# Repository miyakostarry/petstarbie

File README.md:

CATBIE (STARBIE)

A small digital pet that lives inside a cat-shaped case. It shows a pet on a screen and reacts when you move it, press it's buttons or touch it.

How it works╰(*°▽°*)╯

> An ESP32 board is the brain, It runs the pet program.
> A screen shows the pet.
> A gyro sensor feels when you tilt or shake the cat.
> Two buttons and a touch pad let you interact with it.
> A temperature sensor lets the pet react to the room.
> A rechargeable battery powers it. A charger module charges it over USB, and a power switch turns it on and off.

All the parts plug into sockets on a cat-shaped PCB (designed in KiCad). The board sits inside a 3D-printed cat shell.

 Parts  (≧∀≦)ゞ

- ESP32 DevKit V1 (30-pin)
- 1.8" ST7735 SPI TFT display
- MPU6050 (GY-521) gyro
- DHT11 module
- 2 tactile push buttons
- 2 resistors, 100 kΩ
- JST-PH battery connector
- 3.7 V LiPo battery
- TP4056 charger module
- MT3608 boost converter

## Bill of Materials (BOM) (｡•̀ᴗ-)✧

Here's the list of components used for CATBIE, along with their estimated prices and suppliers. Prices may vary depending on availability and shipping.

| Component                                    |   Quantity | Supplier     | Cost per Item (USD) | Total Cost (USD) | Link                                                                                               |
| -------------------------------------------- | ---------: | ------------ | ------------------: | ---------------: | -------------------------------------------------------------------------------------------------- |
| ESP32 DevKit V1 (30-pin)                     |          1 | Amazon India |               $5.60 |            $5.60 | [View product](https://www.amazon.in/SP-ELECTRON-ESP32-Development-ESP32-WROOM-32/dp/B0HD7QC26L/)  |
| MPU6050 (GY-521)                             |          1 | Amazon India |               $3.40 |            $3.40 | [View product](https://www.amazon.in/dp/B07H3XH1TB)                                                |
| 1.8" ST7735 SPI TFT Display                  |          1 | Robu.in      |               $3.50 |            $3.50 | [View product](https://robu.in/product/1-8-inch-spi-128160-tft-lcd-display-module-pcb-arduino/)    |
| DHT11 Temperature and Humidity Sensor Module |          1 | Robu.in      |               $0.56 |            $0.56 | [View product](https://robu.in/product/dht11-digital-relative-humidity-temperature-sensor-module/) |
| Tactile Push Button                          |          1 | Robu.in      |               $0.25 |            $0.25 | [View product](https://robu.in/product/6x6x5-tactile-push-button-switch/)                          |
| 100 kΩ Resistor                              |          2 | Robu.in      |               $0.20 |            $0.40 | [View product](https://robu.in/product/100k-ohm-0-5w-metal-film-resistor-pack-of-50/)              |
| 3.7 V, 500 mAh LiPo Battery with JST-PH      |          1 | Amazon India |   $3.00 (estimated) |            $3.00 | [Search products](https://www.amazon.in/s?k=3.7V+500mAh+lipo+battery+JST+PH)                       |
| TP4056 USB-C Charger Module with Protection  |          1 | Amazon India |               $1.00 |            $1.00 | [View product](https://www.amazon.in/UNIVERSAL-HUB-TP4056-Overcharge-Protection/dp/B0FVLYQBKC/)    |
| MT3608 Boost Converter                       |          1 | Amazon India |               $1.40 |            $1.40 | [View product](https://www.amazon.in/Hexonix-Voltage-Booster-Adjustable-Converter/dp/B0HDP881HN/)  |
| Custom PCB                                   |          1 | JLCPCB       |   $5.20 (estimated) |            $5.20 | [JLCPCB](https://jlcpcb.com/)                                                                      |
| Estimated Shipping                           | 1 shipment | JLCPCB       |                   — |            $9.83 | —                                                                                                  |

### Estimated Project Cost

| Category              | Estimated Cost (USD) |
| --------------------- | -------------------: |
| Electronic components |               $19.11 |
| Custom PCB            |                $5.20 |
| Estimated shipping    |                $9.83 |
| **Estimated Total**   |           **$34.14** |

> **Note:** These are estimated prices, not a confirmed final bill. Shipping, taxes, customs charges, and component prices may change. The battery price is approximate because different sellers offer different options.

AI help is taken to understand how connections and components work and also help taken from people in how to use kiCAD and one of my friend helped me picking up the components to use so yeah he helped alot 
another thing i want to add that my friend created the structure shell for my catbie/neckobie in blender but i'm having trouble opening the fbx file in blender so i couldn't post the image of it

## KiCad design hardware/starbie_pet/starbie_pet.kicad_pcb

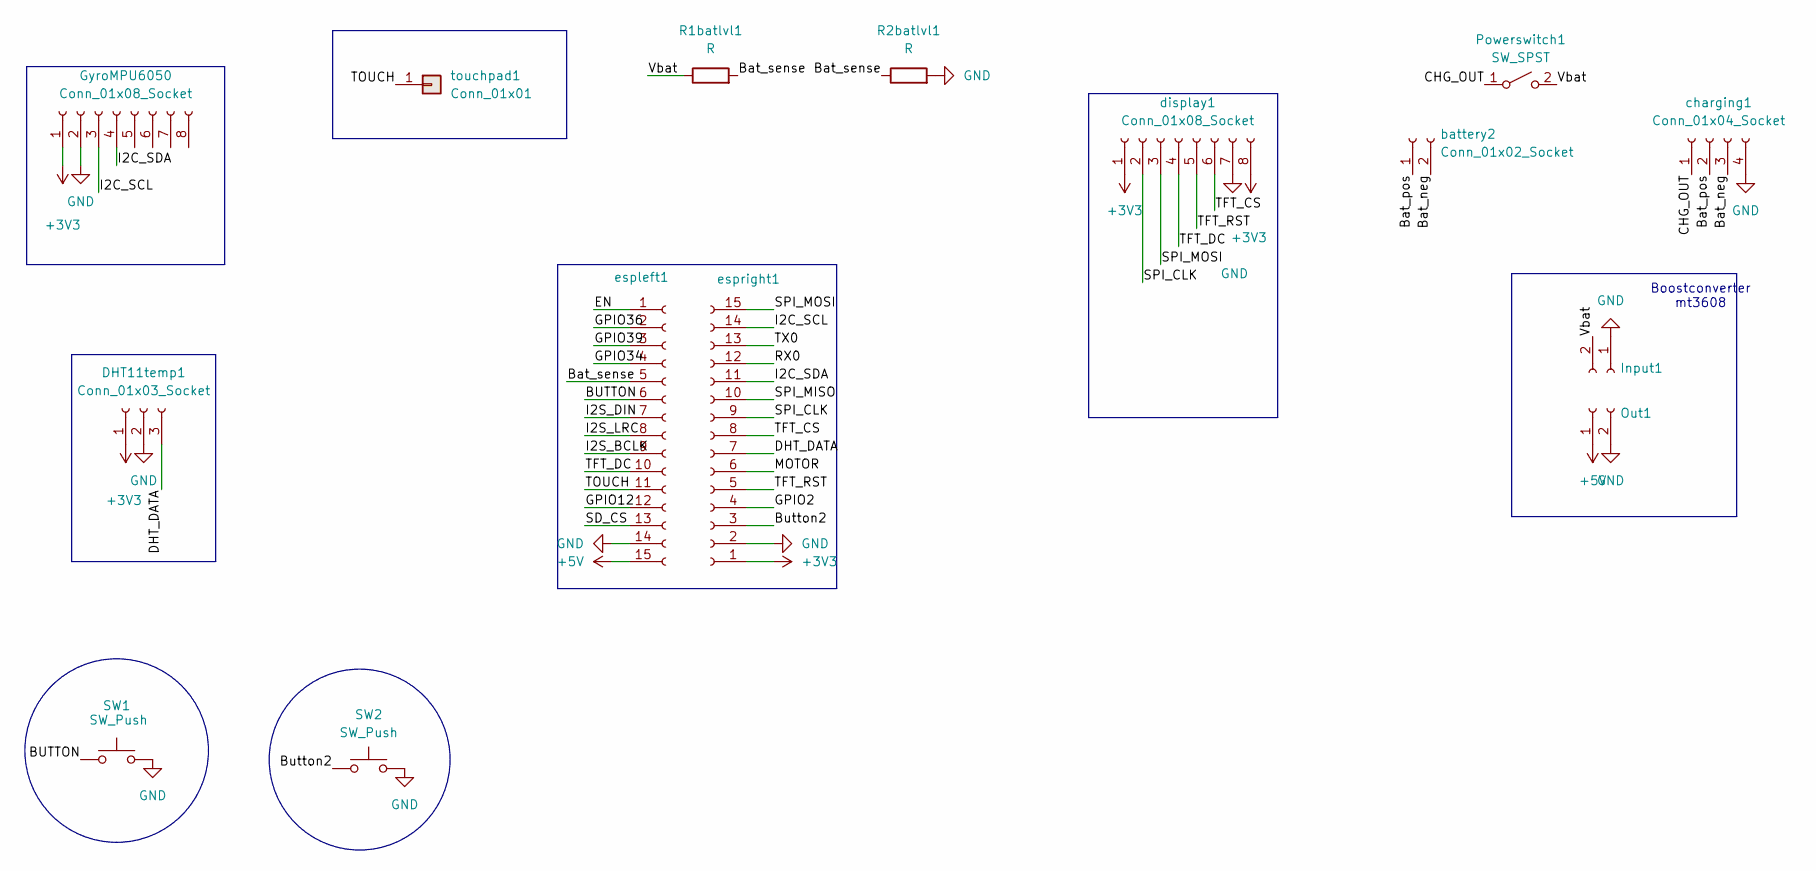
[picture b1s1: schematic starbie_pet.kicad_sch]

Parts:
DHT11temp1: Conn_01x03_Socket; PinSocket_1x03_P2.54mm_Vertical
GyroMPU6050: Conn_01x08_Socket; PinSocket_1x08_P2.54mm_Vertical
Input1: Conn_01x02_Socket; PinHeader_1x02_P2.54mm_Vertical
Out1: Conn_01x02_Socket; PinHeader_1x02_P2.54mm_Vertical
Powerswitch1: SW_SPST; FanPinHeader_1x03_P2.54mm_Vertical
R1batlvl1, R2batlvl1: R; R_Axial_DIN0207_L6.3mm_D2.5mm_P2.54mm_Vertical
SW1, SW2: SW_Push; SW_PUSH_6mm
battery2: Conn_01x02_Socket; JST_PH_B2B-PH-K_1x02_P2.00mm_Vertical
charging1: Conn_01x04_Socket; FanPinHeader_1x04_P2.54mm_Vertical
display1: Conn_01x08_Socket; PinSocket_1x08_P2.54mm_Vertical
espleft1: Conn_01x15_Socket; PinSocket_1x15_P2.54mm_Vertical
espright1: Conn_01x15_Socket; PinSocket_1x15_P2.54mm_Vertical
touchpad1: Conn_01x01; TestPoint_Pad_D4.0mm

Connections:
+3V3: DHT11temp1.1, GyroMPU6050.1, display1.1, display1.8, espright1.1
+5V: Out1.1, espleft1.15
/BUTTON: SW1.1, espleft1.6
/Bat_neg: battery2.2, charging1.3
/Bat_pos: battery2.1, charging1.2
/Bat_sense: R1batlvl1.2, R2batlvl1.1, espleft1.5
/Button2: SW2.1, espright1.3
/CHG_OUT: Powerswitch1.1 (A), charging1.1
/DHT_DATA: DHT11temp1.3, espright1.7
/EN: espleft1.1
/GPIO2: espright1.4
/GPIO12: espleft1.12
/GPIO34: espleft1.4
/GPIO36: espleft1.2
/GPIO39: espleft1.3
/I2C_SCL: GyroMPU6050.3, espright1.14
/I2C_SDA: GyroMPU6050.4, espright1.11
/I2S_BCLK: espleft1.9
/I2S_DIN: espleft1.7
/I2S_LRC: espleft1.8
/MOTOR: espright1.6
/RX0: espright1.12
/SD_CS: espleft1.13
/SPI_CLK: display1.2, espright1.9
/SPI_MISO: espright1.10
/SPI_MOSI: display1.3, espright1.15
/TFT_CS: display1.6, espright1.8
/TFT_DC: display1.4, espleft1.10
/TFT_RST: display1.5, espright1.5
/TOUCH: espleft1.11, touchpad1.1 (Pin_1_1)
/TX0: espright1.13
/Vbat: Input1.2, Powerswitch1.2 (B), R1batlvl1.1
GND: DHT11temp1.2, GyroMPU6050.2, Input1.1, Out1.2, R2batlvl1.2, SW1.2, SW2.2, charging1.4, display1.7, espleft1.14, espright1.2

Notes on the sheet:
Boostconverter mt3608

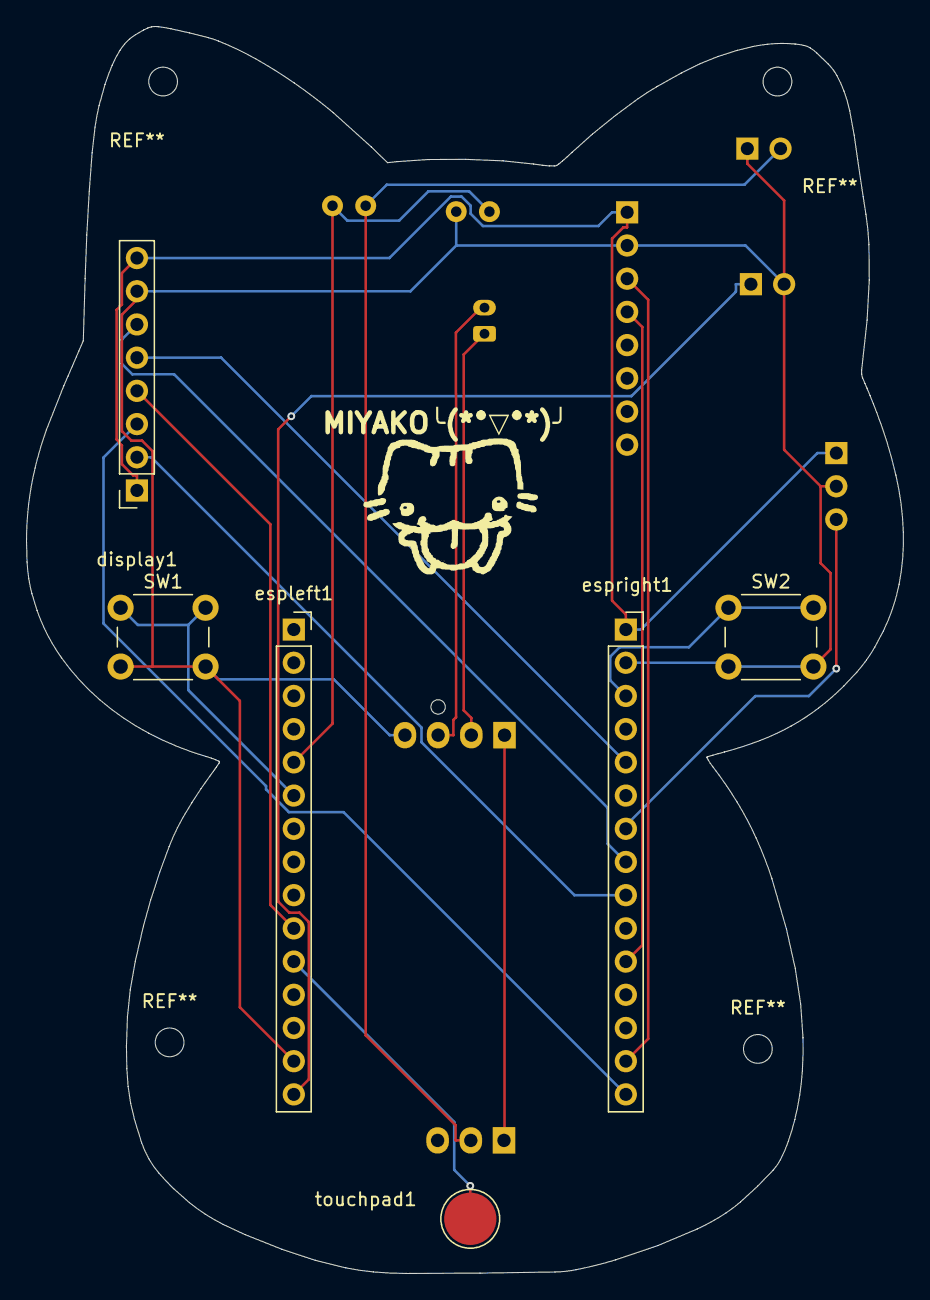
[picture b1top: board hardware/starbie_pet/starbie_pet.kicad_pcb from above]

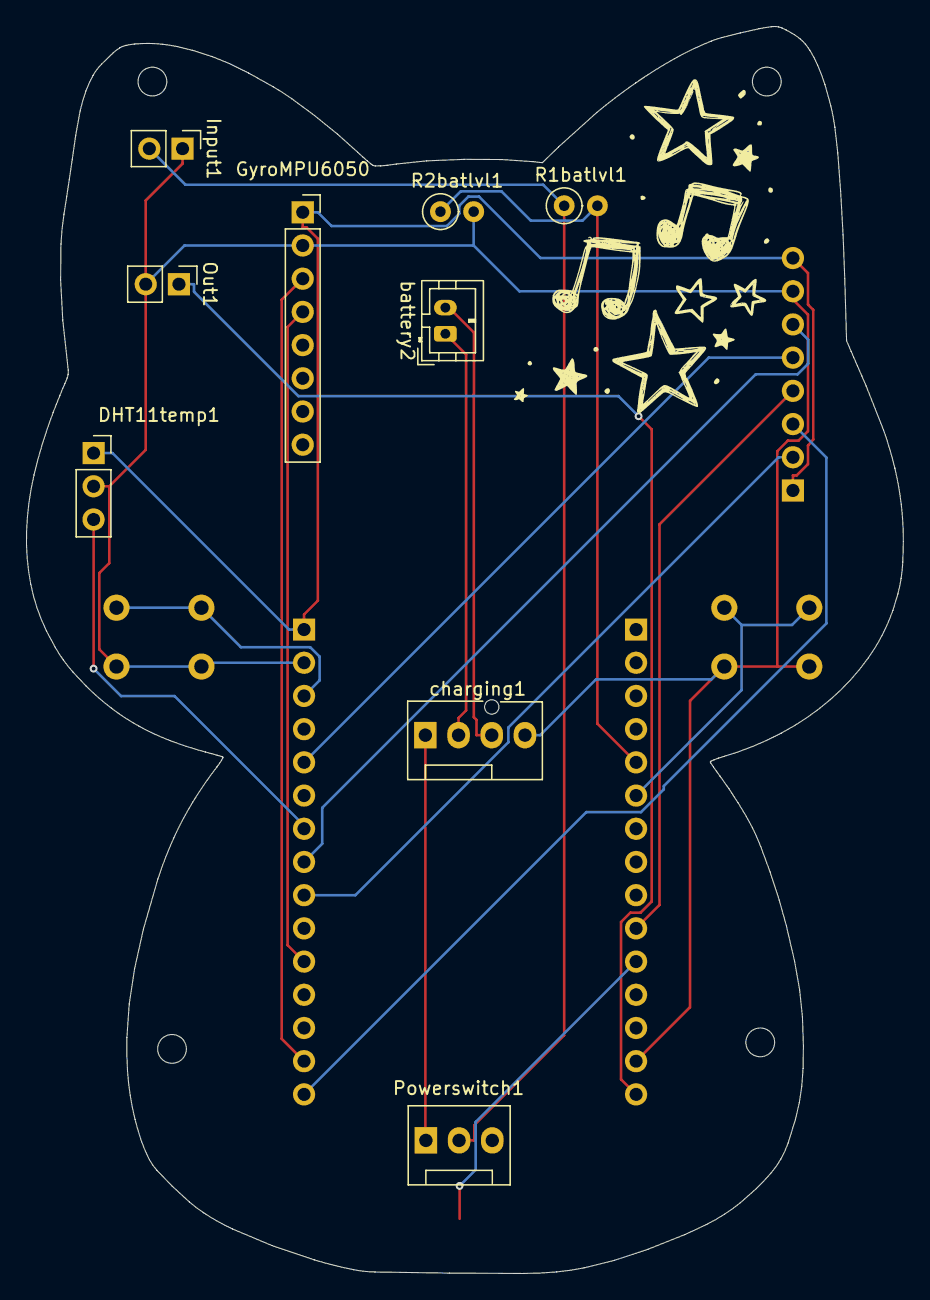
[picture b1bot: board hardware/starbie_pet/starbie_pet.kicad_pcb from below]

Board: 2 copper layers, 67.1 x 95.4 mm, 15 parts (9 on the bottom side), 19 nets.

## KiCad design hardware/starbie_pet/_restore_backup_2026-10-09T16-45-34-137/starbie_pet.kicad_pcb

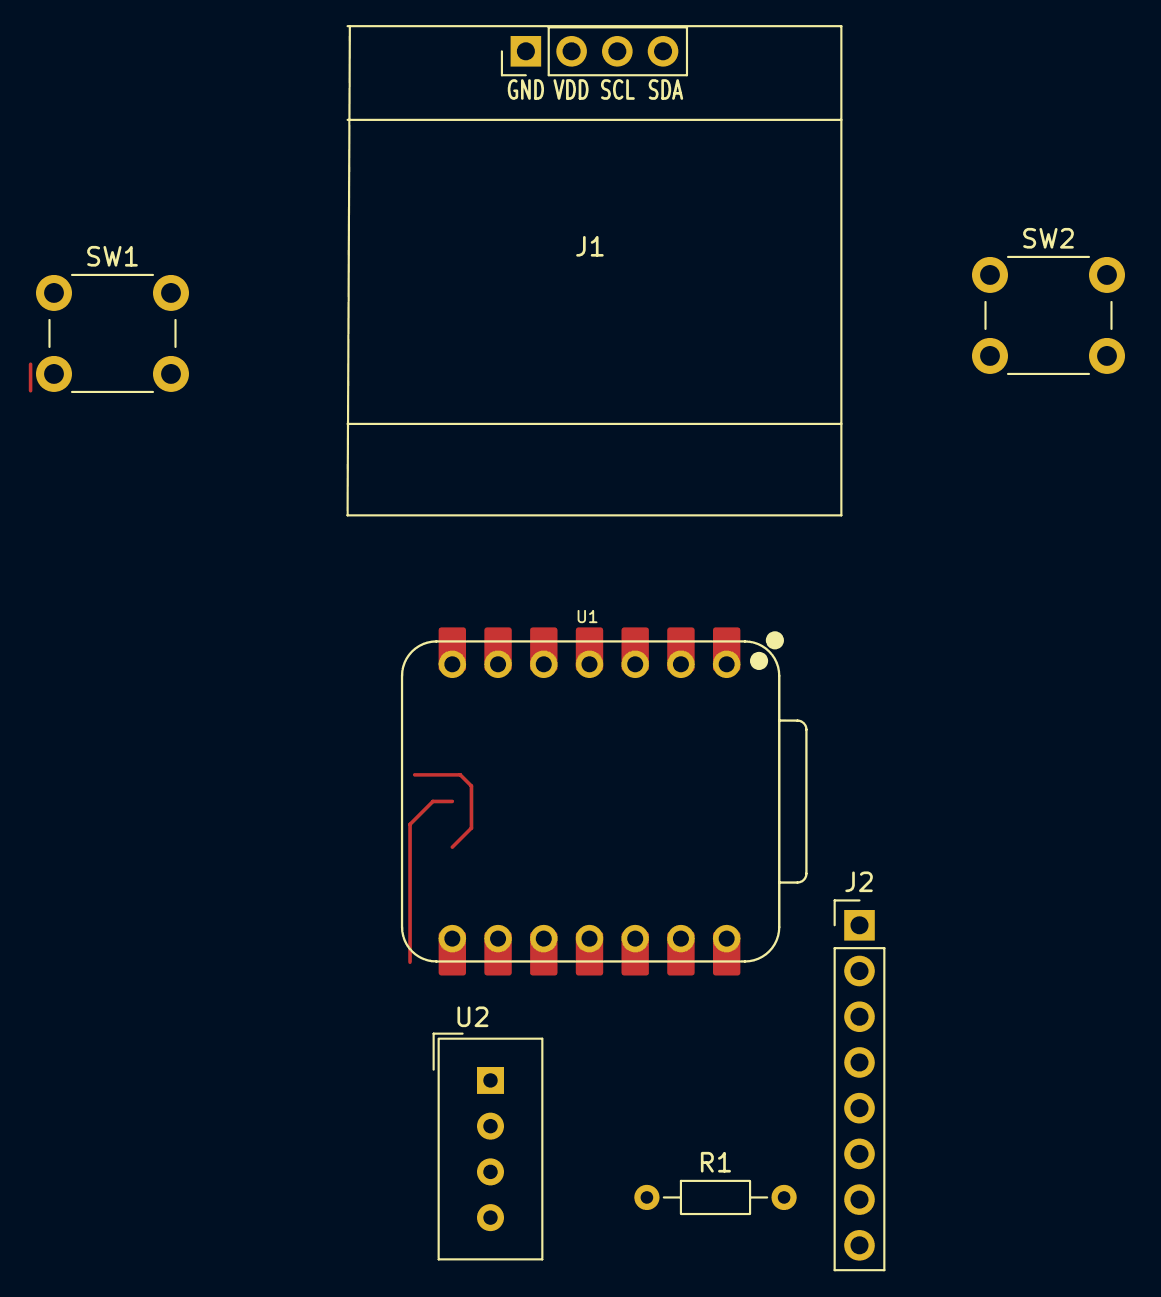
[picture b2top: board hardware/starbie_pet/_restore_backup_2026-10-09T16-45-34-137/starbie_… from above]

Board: 2 copper layers, 11 parts (0 on the bottom side), 7 nets.

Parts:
H1, H2, H3, H4: MountingHole; MountingHole_2.7mm_M2.5
J1: Conn_01x04_Pin; Display_128x64_096_I2C
J2: Conn_01x08_Pin; PinHeader_1x08_P2.54mm_Vertical
R1: 10k; R_Axial_DIN0204_L3.6mm_D1.6mm_P7.62mm_Horizontal
SW1, SW2: SW_Push; SW_PUSH_6mm_H5mm
U1: XIAO-ESP32-C3-SMD; XIAO-ESP32-C6-DIP
U2: DHT11; Aosong_DHT11_5.5x12.0_P2.54mm

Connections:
+3.3V: J1.2, J2.2, R1.1, U1.12 (3V3_OUT), U2.1 (VDD)
/DHT11 DATA: R1.2, U1.4 (D3), U2.2 (DATA)
/SCL: J1.3, J2.3, U1.5 (D4)
/SDA: J1.4, J2.4, U1.6 (D5)
GND: J1.1, J2.1, SW1.1, SW2.1, U1.13 (GND), U2.4 (GND)
unnamed: SW2.2, U1.2 (D1)
unnamed: SW1.2, U1.3 (D2)

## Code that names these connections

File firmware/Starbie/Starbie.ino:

#include <Wire.h>
#include <Adafruit_GFX.h>
#include <Adafruit_ST7735.h>
#include <Adafruit_MPU6050.h>
#include <DHT.h>
#include <Adafruit_Sensor.h>

// DISPLAY
const int TFT_CS = 5;
const int TFT_DC = 27;
const int TFT_RST = 4;

// ESP

const int BUTTON1 =32;
const int BUTTON2 =15;
const int DHT_DATA =17;
const int TOUCH =14;
const int BAT_SENSE = 35;
const int MOTOR = 27;


//default one - MISO , CLK ,MOSI


// i2c connect
// SCL = 22 and SDA = 21 are already defined by the ESP32 board package

const bool USE_DHT = true;



Adafruit_ST7735 tft = Adafruit_ST7735(TFT_CS,TFT_DC,TFT_RST);

const int TOUCH_LIMIT = 50;
bool happy1=false;
unsigned long happyStart =0;
unsigned long lastBlink =0;




void clearFace(){
  tft.fillRect(0,30,128,100,ST77XX_BLUE);
}
void drawEye(){
  clearFace();
  tft.fillCircle(40,60,10,ST77XX_ORANGE);
  tft.fillCircle(88,60,10,ST77XX_ORANGE);
}

void sleepEye(){
  tft.fillRect(30 , 59,20,3 ,ST77XX_ORANGE);
  tft.fillRect(78 , 59,20,3 ,ST77XX_ORANGE);
}
void happy(){
  tft.drawLine(30,68,40,55,ST77XX_ORANGE);
  tft.drawLine(40,55,50,68,ST77XX_ORANGE);


  tft.drawLine(78,68,88,55,ST77XX_ORANGE);
  tft.drawLine(88,55,98,68,ST77XX_ORANGE);
}

void setup(){
  tft.initR(INITR_BLACKTAB);
  tft.fillScreen(ST77XX_BLUE);
  drawEye();
  lastBlink =millis();
  
}
void loop(){
  bool touched = (touchRead(TOUCH)<TOUCH_LIMIT);
  if (touched && !happy1){
    happy1 = true;
    happyStart = millis();
    happy();
  }
  if (happy1 && millis() - happyStart > 2000){
    happy1 = false;
    drawEye();
    lastBlink = millis();
  }
  if(!happy1 && millis() -lastBlink >3000){
    sleepEye();
    delay(200);
    drawEye();
    lastBlink = millis();
  }

  delay(20);
}
